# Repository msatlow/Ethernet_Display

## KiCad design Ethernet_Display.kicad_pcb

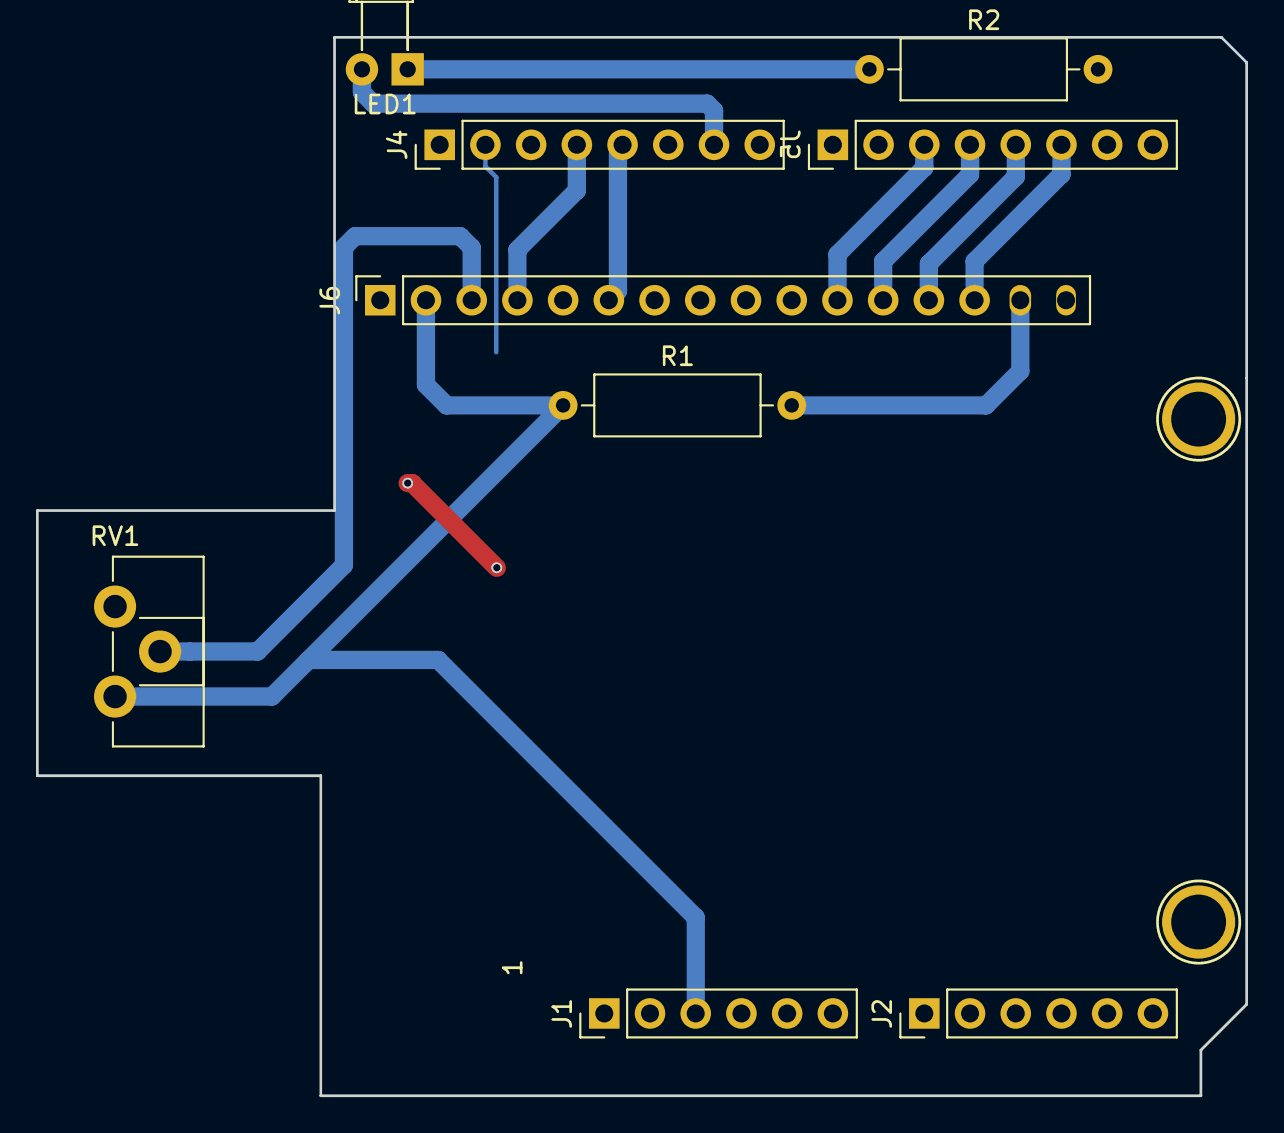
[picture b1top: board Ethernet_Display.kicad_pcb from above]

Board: 2 copper layers, 67.2 x 58.8 mm, 11 parts (0 on the bottom side), 12 nets.

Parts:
J1: Power; PinHeader_1x06_P2.54mm_Vertical
J2: Analog; PinHeader_1x06_P2.54mm_Vertical
J4, J5: Digital; PinHeader_1x08_P2.54mm_Vertical
J6: Conn_01x16; PinSocket_1x16_P2.54mm_Vertical
LED1: LED; LED_D3.0mm_Horizontal_O3.81mm_Z2.0mm
P6, P8: CONN_01X01; Arduino_1pin
R1: 220; R_Axial_DIN0309_L9.0mm_D3.2mm_P12.70mm_Horizontal
R2: 100; R_Axial_DIN0309_L9.0mm_D3.2mm_P12.70mm_Horizontal
RV1: R_POT_TRIM_US; Potentiometer_Piher_PT-10-H01_Horizontal

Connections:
+5V: J1.3, J6.2, R1.1, RV1.3
D2: J5.6, J6.14
D3: J5.5, J6.13
D4: J5.4, J6.12
D5: J5.3, J6.11
D9: J4.7, LED1.2
D11: J4.5, J6.6
D12: J4.4, J6.4
GND: J1.4, J1.5, J4.2, J6.1, J6.5, J6.16, R2.2, RV1.1
unnamed: J6.3, RV1.2
unnamed: J6.15, R1.2
unnamed: LED1.1, R2.1

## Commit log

2019-07-02 initial
2019-07-03 iteration step 2
2019-07-03 added display.stl
2019-07-04 save
2019-11-22 Fixup wrong wiring
2019-11-22 new version
